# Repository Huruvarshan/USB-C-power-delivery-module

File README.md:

# USB-C-power-delivery-module
Repo for my USB-C power supply delivery module

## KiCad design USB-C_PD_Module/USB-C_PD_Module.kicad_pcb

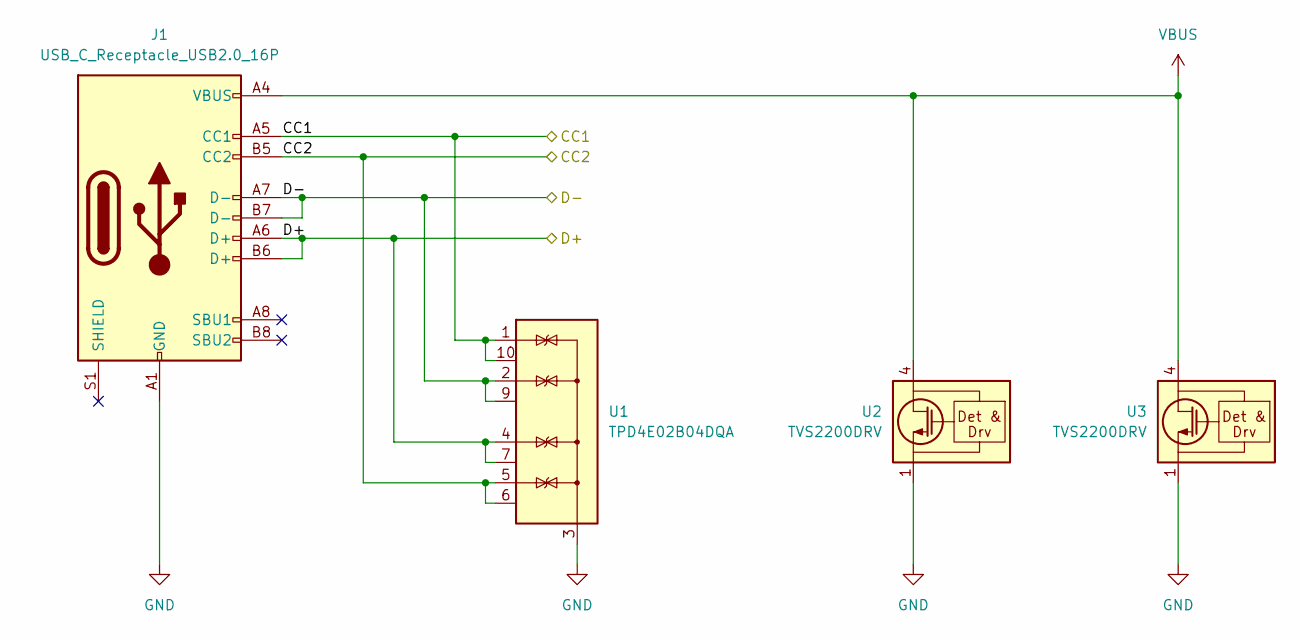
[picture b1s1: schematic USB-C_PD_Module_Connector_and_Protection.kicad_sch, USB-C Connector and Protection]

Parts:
J1: USB_C_Receptacle_USB2.0_16P; USB_C_Receptacle_GCT_USB4105-xx-A_16P_TopMnt_Horizontal
U1: TPD4E02B04DQA; USON-10_2.5x1.0mm_P0.5mm
U2, U3: TVS2200DRV; WSON-6-1EP_2x2mm_P0.65mm_EP1x1.6mm

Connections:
/D+: J1.A6 (D+), J1.B6 (D+), U1.4 (IO3), U1.7 (NC); also elsewhere on the board
/D-: J1.A7 (D-), J1.B7 (D-), U1.2 (IO2), U1.9 (NC); also elsewhere on the board
/USB-C Connector and Protection/CC1: J1.A5 (CC1), U1.1 (IO1), U1.10 (NC); also elsewhere on the board
/USB-C Connector and Protection/CC2: J1.B5 (CC2), U1.5 (IO4), U1.6 (NC); also elsewhere on the board
GND: J1.A1 (GND), J1.A12 (GND), J1.B1 (GND), J1.B12 (GND), U1.3 (G), U1.8 (G), U2.1 (GND), U2.2 (GND), U2.3 (GND), U2.7 (GND), U3.1 (GND), U3.2 (GND), U3.3 (GND), U3.7 (GND); also elsewhere on the board
VBUS: J1.A4 (VBUS), J1.A9 (VBUS), J1.B4 (VBUS), J1.B9 (VBUS), U2.4 (IN), U2.5 (IN), U2.6 (IN), U3.4 (IN), U3.5 (IN), U3.6 (IN); also elsewhere on the board

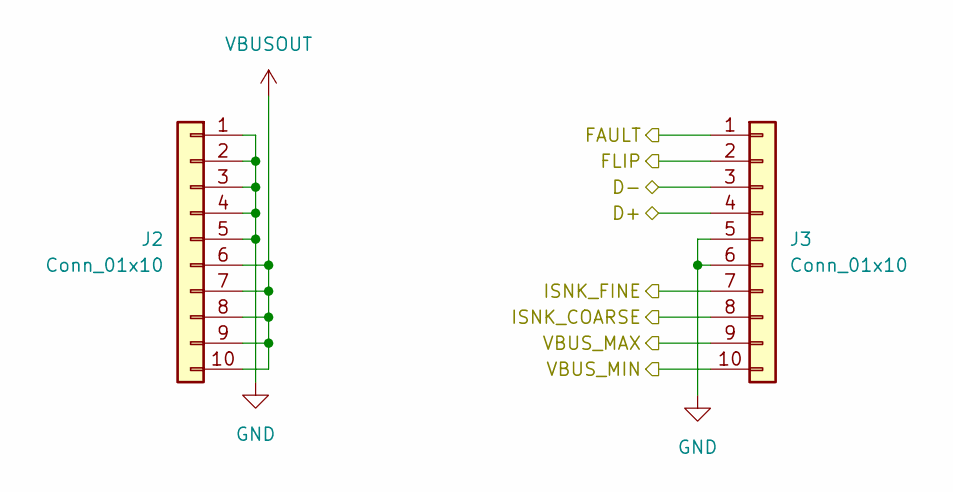
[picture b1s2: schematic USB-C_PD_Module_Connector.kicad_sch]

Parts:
J2, J3: Conn_01x10; PinHeader_1x10_P2.54mm_Vertical

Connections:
/Connector/FAULT: J3.1; also elsewhere on the board
/Connector/FLIP: J3.2; also elsewhere on the board
/Connector/ISNK_COARSE: J3.8; also elsewhere on the board
/Connector/ISNK_FINE: J3.7; also elsewhere on the board
/Connector/VBUS_MAX: J3.9; also elsewhere on the board
/Connector/VBUS_MIN: J3.10; also elsewhere on the board
/D+: J3.4; also elsewhere on the board
/D-: J3.3; also elsewhere on the board
GND: J2.1, J2.2, J2.3, J2.4, J2.5, J3.5, J3.6; also elsewhere on the board
VBUSOUT: J2.6, J2.7, J2.8, J2.9, J2.10; also elsewhere on the board

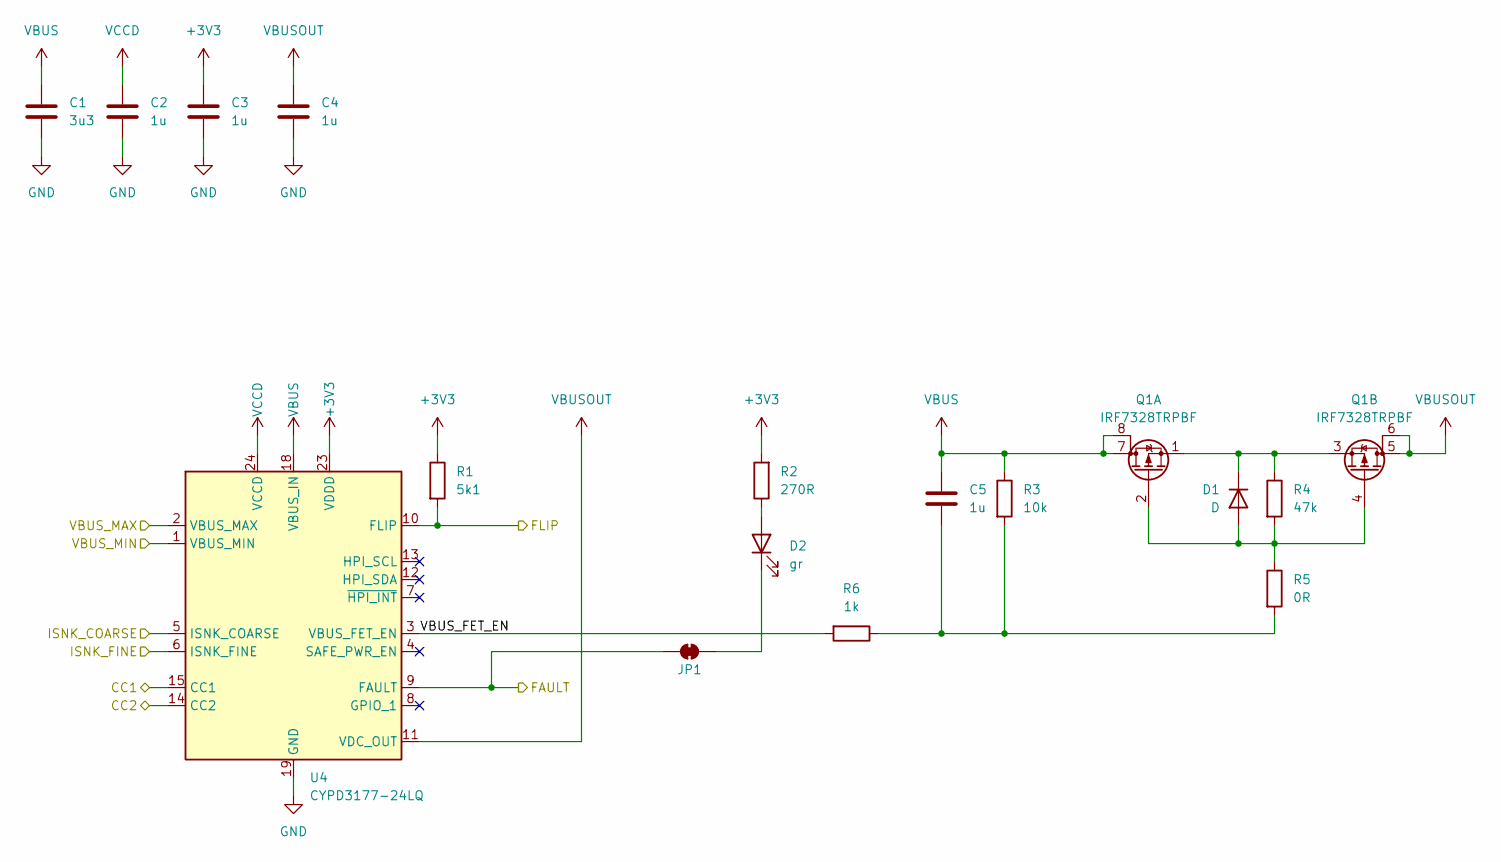
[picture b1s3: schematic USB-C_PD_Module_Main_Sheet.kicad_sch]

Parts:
C1: 3u3; C_0805_2012Metric
C2, C3, C4, C5: 1u; C_0805_2012Metric
D1: D; D_SOD-123
D2: gr; LED_0603_1608Metric
JP1: SolderJumper_2_Bridged; SolderJumper-2_P1.3mm_Bridged_RoundedPad1.0x1.5mm
Q1: IRF7328TRPBF; SO-8_3.9x4.9mm_P1.27mm
R1: 5k1; R_0805_2012Metric
R2: 270R; R_0805_2012Metric
R3: 10k; R_0805_2012Metric
R4: 47k; R_0805_2012Metric
R5: 0R; R_0805_2012Metric
R6: 1k; R_0805_2012Metric
U4: CYPD3177-24LQ; QFN-24-1EP_4x4mm_P0.5mm_EP2.75x2.75mm

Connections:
+3V3: C3.1, R1.1, R2.2, U4.23 (VDDD)
/Connector/FAULT: JP1.2 (B), U4.9 (FAULT); also elsewhere on the board
/Connector/FLIP: R1.2, U4.10 (FLIP); also elsewhere on the board
/Connector/ISNK_COARSE: U4.5 (ISNK_COARSE); also elsewhere on the board
/Connector/ISNK_FINE: U4.6 (ISNK_FINE); also elsewhere on the board
/Connector/VBUS_MAX: U4.2 (VBUS_MAX); also elsewhere on the board
/Connector/VBUS_MIN: U4.1 (VBUS_MIN); also elsewhere on the board
/Main Sheet/VBUS_FET_EN: R6.2, U4.3 (VBUS_FET_EN)
/USB-C Connector and Protection/CC1: U4.15 (CC1); also elsewhere on the board
/USB-C Connector and Protection/CC2: U4.14 (CC2); also elsewhere on the board
GND: C1.2, C2.2, C3.2, C4.2, U4.19 (GND), U4.22 (GND), U4.25 (GND); also elsewhere on the board
unnamed: C5.2, R3.2, R5.2, R6.1
unnamed: D1.2 (A), Q1.2 (G), Q1.4 (G), R4.2, R5.1
unnamed: D1.1 (K), Q1.1 (S), Q1.3 (S), R4.1
unnamed: D2.2 (A), R2.1
unnamed: D2.1 (K), JP1.1 (A)
VBUS: C1.1, C5.1, Q1.7 (D), Q1.8 (D), R3.1, U4.18 (VBUS_IN); also elsewhere on the board
VBUSOUT: C4.1, Q1.5 (D), Q1.6 (D), U4.11 (VDC_OUT); also elsewhere on the board
VCCD: C2.1, U4.24 (VCCD)

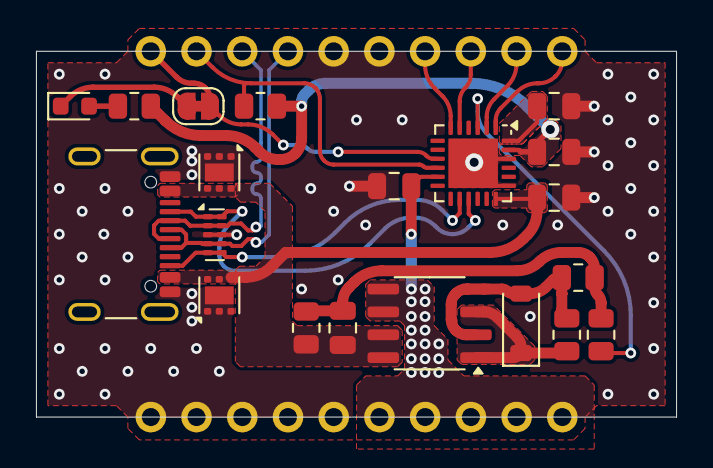
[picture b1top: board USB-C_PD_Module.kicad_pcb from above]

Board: 4 copper layers, 35.6 x 20.3 mm, 22 parts (0 on the bottom side), 21 nets.

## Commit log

2025-01-24 Creation of Kicad Project
2025-01-24 Almost all. Missing connector
2025-01-27 Snap to Grid
2025-01-30 Module Basics
2025-02-25 Layout Finished
2025-03-04 Changed file structure and finalized PCB
2025-03-04 First Panel
2025-03-04 Add footprint
2025-03-04 add 3d file to libary
2025-03-04 umbennent
2025-03-04 Finalized V1 PCB panel
2025-03-25 withouut panel
2025-05-18 File restructuring
